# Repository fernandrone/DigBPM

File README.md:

DigBPM
======

Digital Blood Pressure Meter

Test PR

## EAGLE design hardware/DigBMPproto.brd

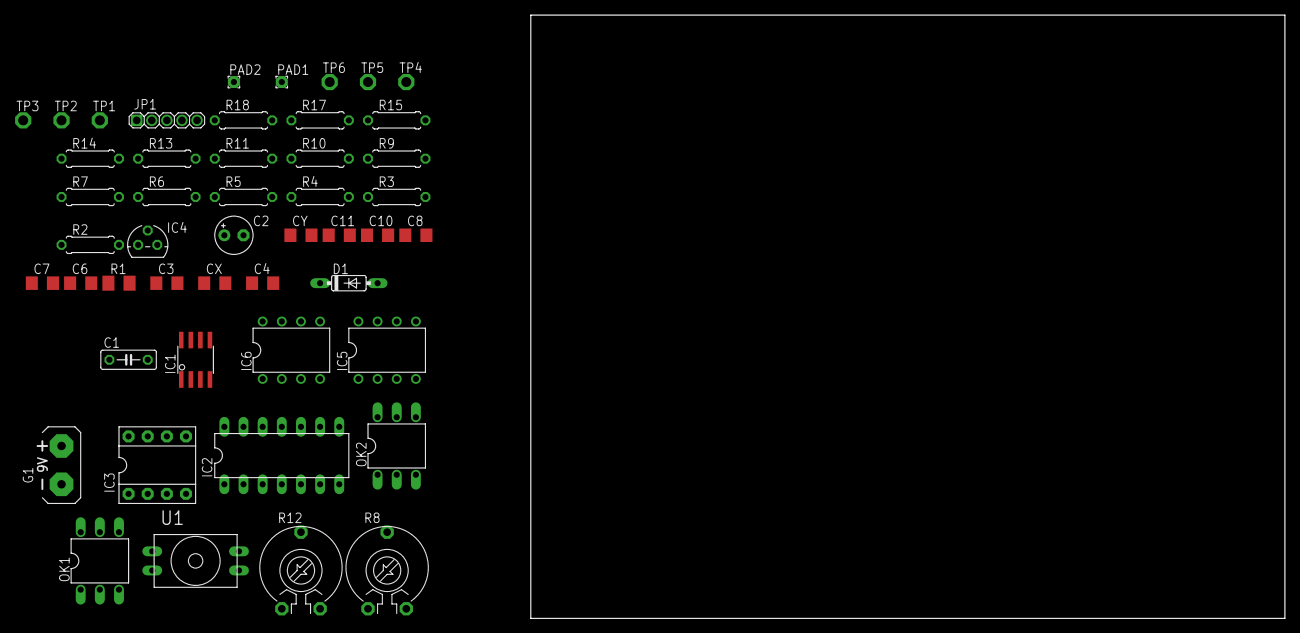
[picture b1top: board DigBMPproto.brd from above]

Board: 2 copper layers, 100.0 x 80.0 mm, 48 parts (0 on the bottom side), 24 nets, no tracks yet.

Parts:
C1: 100n; C050-025X075
C2: 10u; E2,5-5
C3: 100n; C3216
C4: 100nF; C3216
C6, C7, C8, C11: 1u; C3216
C10: 10u; C3216
CX: 47nF; C3216
CY: 47n; C3216
D1: 1N4148DO35-7; DO35-7
G1: AB9V
IC1: INA126U; SO08
IC2: TL084P; DIL14
IC3: REF102P; DIL08
IC4: 7805L; TO92
IC5, IC6: OP07Z; DIL08
JP1: 1_05X2MM
OK1, OK2: 4N35; DIL06
PAD1, PAD2: 1,6/0,8
R1: 1.2k; M1206
R2, R4: 82k; 0207/7
R3, R5: 150k; 0207/7
R6: 56k; 0207/7
R7: 8.2k; 0207/7
R8, R12: PT-10
R9: 10k; 0207/7
R10: 220k; 0207/7
R11: 12k; 0207/7
R13: 470k; 0207/7
R14, R17: 100k; 0207/7
R15: 1k; 0207/7
R18: 470K; 0207/7
TP1, TP2, TP3, TP4, TP5, TP6: PTR1PAD1-13; P1-13
U1: TBP_AN

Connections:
GND: CX.2, CY.2, IC1.5, IC2.1, IC2.2, IC2.9, IC2.13, IC3.4, R7.1, R9.1, R11.1, R15.1, U1.3
unnamed: IC2.3, R13.1, R18.2
unnamed: IC2.7, R2.1, R6.2, TP4.TP
unnamed: IC1.1, R1.2
unnamed: IC1.8, R1.1
unnamed: IC2.10, R3.2
unnamed: C4.1, CX.1, R2.2, R3.1
unnamed: IC5.6, IC6.3, R10.2, R14.2, TP5.TP
unnamed: IC6.6, R4.1, R17.2, TP6.TP
unnamed: C10.2, IC5.3
unnamed: C3.1, CY.1, R4.2, R5.1
unnamed: IC2.6, R7.2, R12.1
unnamed: C3.2, IC2.14
unnamed: R6.1, R12.2
unnamed: IC5.2, R9.2, R14.1
unnamed: C6.2, C7.2, C8.2, C10.1, C11.2, R10.1, R11.2
unnamed: IC6.2, R8.1, R15.2
unnamed: IC2.12, R5.2
unnamed: R8.2, R17.1
V+: C1.1, C2.+, G1.+, IC1.3, IC1.7, IC2.4, IC3.2, IC4.3, IC5.7, IC6.7, R13.2, TP1.TP
V-: C1.2, C2.-, G1.-, IC1.2, IC1.4, IC2.11, IC4.2, IC5.4, IC6.4, R18.1, TP2.TP
VCC: IC3.6, U1.1
V_INA: C6.1, C7.1, C8.1, C11.1, IC1.6, IC2.5, TP3.TP
V_PRE: C4.2, IC2.8

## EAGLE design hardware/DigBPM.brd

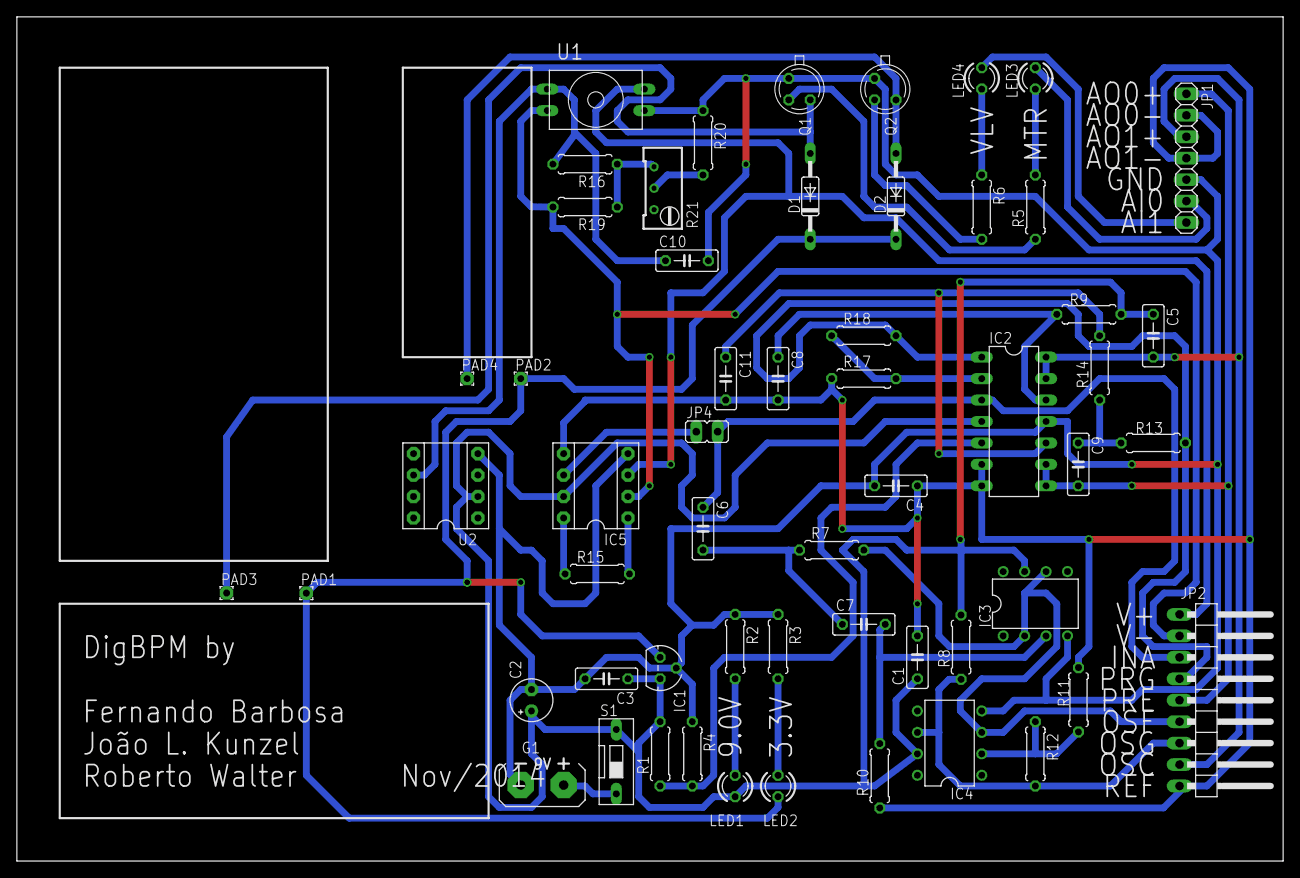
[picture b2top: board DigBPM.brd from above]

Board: 2 copper layers, 150.0 x 100.0 mm, 56 parts (0 on the bottom side), 38 nets.

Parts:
C1, C3, C4, C5, C10: 100n; C050-025X075
C2: 10u; E2,5-5
C6, C7: 10u; C050-025X075
C8: 47n; C050-025X075
C9: 100nF; C050-025X075
C11: 47nF; C050-025X075
D1, D2: 1N4148DO35-10; DO35-10
G1: AB9V
IC1: 7805L; TO92
IC2: TL084P; DIL14
IC3, IC4: OP07Z; DIL08
IC5: INA126P; DIL08
JP1: 1X07
JP2: 1X09/90
JP4: JP1
LED1, LED2, LED3, LED4: LED3MM
PAD1, PAD2, PAD3, PAD4: 1,6/0,8
Q1, Q2: 2N2222; TO18
R1: 470k; 0207/7
R2: 680; 0207/7
R3: 150; 0207/7
R4, R19: 470K; 0207/7
R5, R6: 330; 0207/7
R7: 27k; 0207/7
R8, R13: 82k; 0207/7
R9, R14: 150k; 0207/7
R10: 56k; 0207/7
R11, R15: 1k; 0207/7
R12: 180k; 0207/7
R16, R17, R20: 100k; 0207/7
R18: 270k; 0207/7
R21: 20k; RTRIM64W
S1: DS-01
U1: TBPDANS005PG; TBP_AN
U2: REF02; DIL08

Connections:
4.5V: C1.2, C4.1, C8.2, C11.2, IC2.6, IC2.7, IC5.5, JP1.2, JP1.4, JP2.9, R10.1, R11.1, R17.1
+3V3: D1.C, D2.C, IC1.1, LED2.A, PAD1.1, PAD2.1
+9V: C1.1, C2.+, C3.1, IC1.3, IC2.4, IC3.7, IC4.7, IC5.7, LED1.A, R1.2, S1.2, U2.2
GND: C2.-, C3.2, C4.2, C10.2, G1.-, IC1.2, IC2.11, IC3.4, IC4.4, IC5.4, JP1.5, Q1.1, Q2.1, R2.1, R3.1, R4.1, R20.1, U1.3, U2.4
INA: C6.1, IC2.3, JP2.3, JP4.2
MTR: JP1.6, LED3.A
unnamed: IC2.5, R1.1, R4.2
unnamed: LED3.K, R5.2
unnamed: IC5.1, R15.2
unnamed: IC5.8, R15.1
unnamed: C11.1, IC2.10, R14.2
unnamed: C9.1, R13.2, R14.1
unnamed: IC5.6, JP4.1
unnamed: C7.2, IC3.3, R10.2
unnamed: C5.1, R8.2, R9.1
unnamed: IC2.2, R17.2, R18.1
unnamed: D2.A, PAD4.1, Q2.3
unnamed: LED4.K, R6.1
unnamed: C6.2, C7.1, R7.1
unnamed: LED2.K, R3.2
unnamed: IC4.2, R11.2, R12.1
unnamed: C8.1, IC2.12, R9.2
unnamed: LED1.K, R2.2
unnamed: D1.A, PAD3.1, Q1.3
unnamed: G1.+, S1.1
unnamed: Q1.2, R5.1
unnamed: Q2.2, R6.2
unnamed: R16.1, R19.1, R21.1
unnamed: R20.2, R21.2
OSC: C5.2, IC2.13, IC2.14, JP1.3, JP2.8
OSF: IC3.2, IC3.6, IC4.3, JP2.6, R7.2
OSG: IC4.6, JP2.7, R8.1, R12.2
PRE: C9.2, IC2.8, IC2.9, JP1.1, JP2.5
PRG: IC2.1, JP2.4, R13.1, R18.2
V+: IC5.3, JP2.1, U1.4
V-: IC5.2, JP2.2, R19.2, U1.2
VCC: C10.1, R16.2, U1.1, U2.6
VLV: JP1.7, LED4.A

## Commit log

2014-09-21 Update LICENSE
2014-10-12 First commit.
2014-10-24 MATLAB linear fit
2014-11-17 Eagle Schematic
2014-11-21 LabView VI redone
2014-11-22 LabView and Schematic update
2016-10-12 Test PR
